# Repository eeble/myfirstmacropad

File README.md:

# myfirstmacropad
My First Macro Pad

I'll try to keep this updated.

<br />This work is licensed under a <a rel="license" href="http://creativecommons.org/licenses/by-sa/4.0/">Creative Commons Attribution-ShareAlike 4.0 International License</a>.

This macropad will use QMK as its firmware. QMK is also open source and available from https://qmk.fm/

### Front and Back renders

### BOM
Interactive [BOM](kicad/bom/ibom.html)

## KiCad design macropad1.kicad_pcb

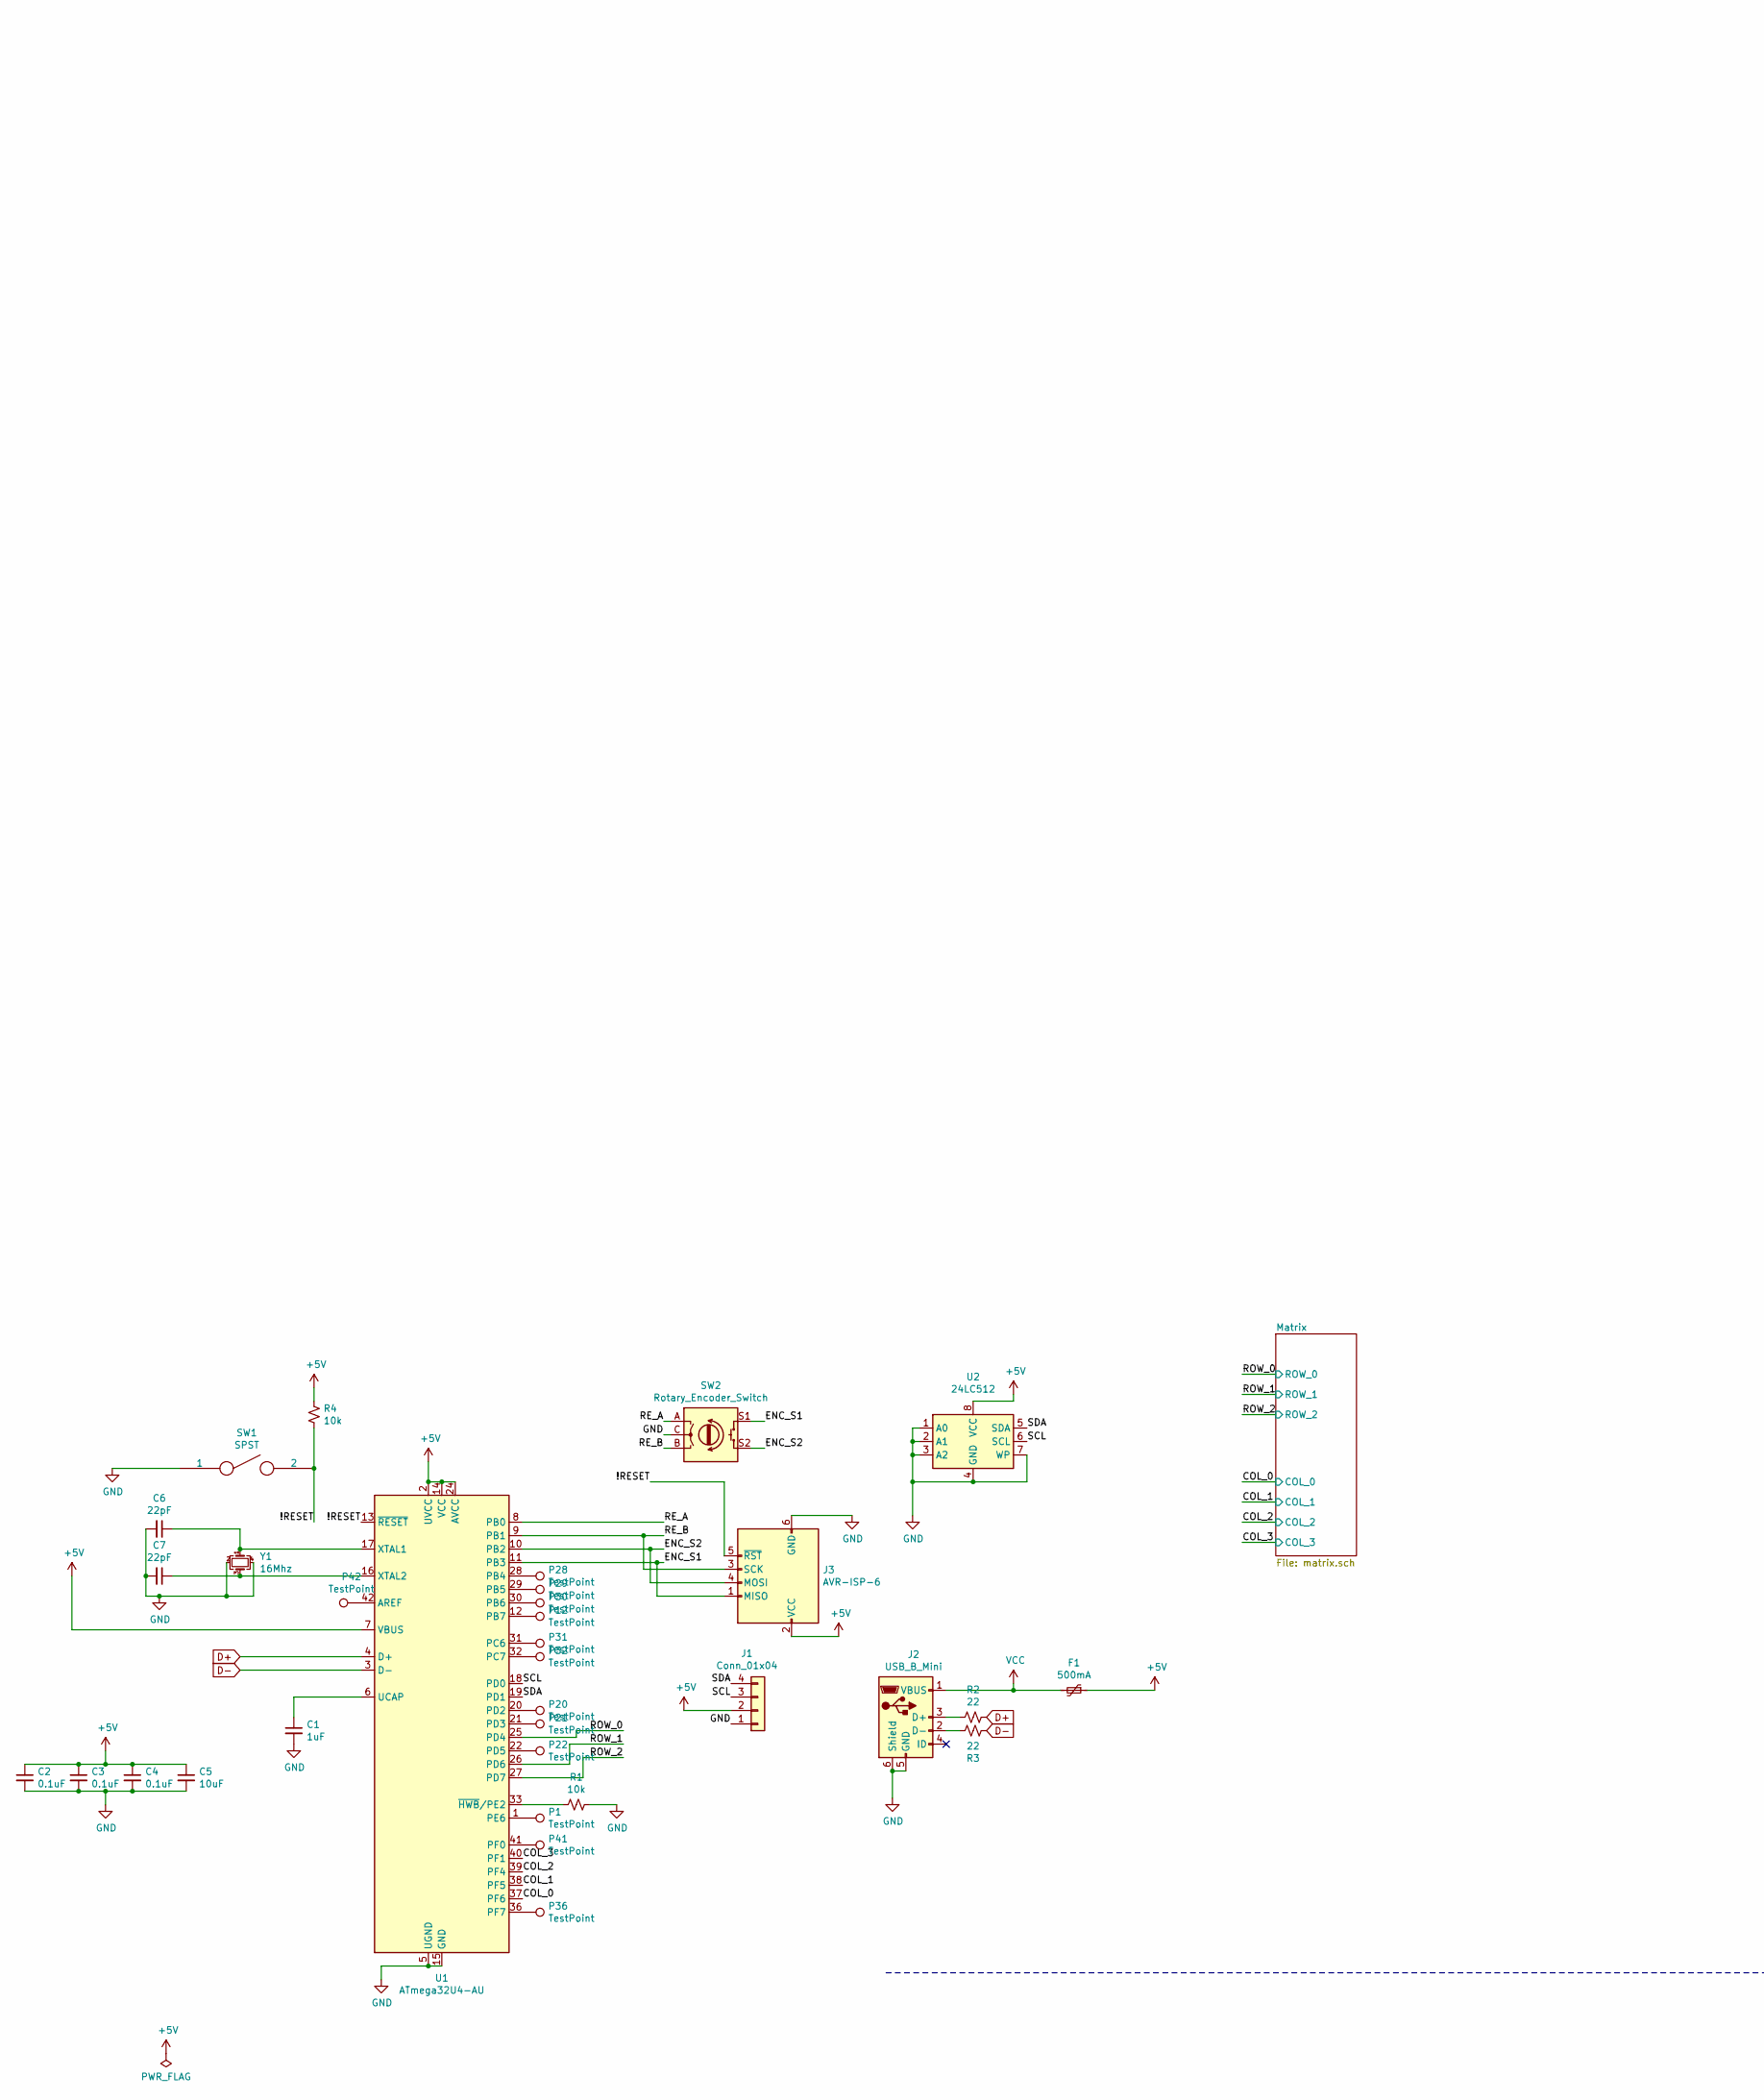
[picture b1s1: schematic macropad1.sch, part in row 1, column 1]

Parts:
C1: 1uF; C_0805_2012Metric
C2, C3, C4: 0.1uF; C_0805_2012Metric
C5: 10uF; C_0805_2012Metric
C6, C7: 22pF; C_0805_2012Metric
F1: 500mA; Fuse_1206_3216Metric
J1: Conn_01x04; OLED_0.91in_4pin
J2: USB_B_Mini; USB_Mini-B_Lumberg_2486_01_Horizontal
J3: AVR-ISP-6; PinHeader_2x03_P2.54mm_Vertical
P1, P12, P20, P21, P22, P28, P29, P30, P31, P32, P36, P41, P42: TestPoint; TestPoint_Pad_D1.0mm
R1, R4: 10k; R_0805_2012Metric
R2, R3: 22; R_0805_2012Metric
SW1: SPST; SW_SPST_REED_CT05-XXXX-G1
SW2: Rotary_Encoder_Switch; RotaryEncoder_Alps_EC11E-Switch_Vertical_H20mm
U1: ATmega32U4-AU; TQFP-44_10x10mm_P0.8mm
U2: 24LC512; TSSOP-8_4.4x3mm_P0.65mm
Y1: 16Mhz; Crystal_SMD_3225-4Pin_3.2x2.5mm_HandSoldering

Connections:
+5V: C2.1, C3.1, C4.1, C5.1, F1.1, J1.2, J3.2 (VCC), R4.1, U1.2 (UVCC), U1.7 (VBUS), U1.14 (VCC), U1.24 (AVCC), U1.34 (VCC), U1.44 (AVCC), U2.8 (VCC); also elsewhere on the board
/!RESET: J3.5 (~RST), R4.2, SW1.2, U1.13 (~RESET)
/COL_0: U1.37 (PF6); also elsewhere on the board
/COL_1: U1.38 (PF5); also elsewhere on the board
/COL_2: U1.39 (PF4); also elsewhere on the board
/COL_3: U1.40 (PF1); also elsewhere on the board
/ENC_S1: J3.1 (MISO), SW2.S1, U1.11 (PB3)
/ENC_S2: J3.4 (MOSI), SW2.S2, U1.10 (PB2)
/PWM1: P12.1, U1.12 (PB7); also elsewhere on the board
/RE_A: SW2.A, U1.8 (PB0)
/RE_B: J3.3 (SCK), SW2.B, U1.9 (PB1)
/ROW_0: U1.25 (PD4); also elsewhere on the board
/ROW_1: U1.26 (PD6); also elsewhere on the board
/ROW_2: U1.27 (PD7); also elsewhere on the board
/SCL: J1.3, U1.18 (PD0), U2.6 (SCL)
/SDA: J1.4, U1.19 (PD1), U2.5 (SDA)
/status_led: P22.1, U1.22 (PD5); also elsewhere on the board
D+: R2.1, U1.4 (D+)
D-: R3.2, U1.3 (D-)
GND: C1.2, C2.2, C3.2, C4.2, C5.2, C6.2, C7.2, J1.1, J2.5 (GND), J2.6 (Shield), J3.6 (GND), R1.1, SW1.1, SW2.C, U1.5 (UGND), U1.15 (GND), U1.23 (GND), U1.35 (GND), U1.43 (GND), U2.1 (A0), U2.2 (A1), U2.3 (A2), U2.4 (GND), U2.7 (WP), Y1.2, Y1.4; also elsewhere on the board
unnamed: C1.1, U1.6 (UCAP)
unnamed: C6.1, U1.17 (XTAL1), Y1.1
unnamed: C7.1, U1.16 (XTAL2), Y1.3
unnamed: J2.2 (D-), R3.1
unnamed: J2.3 (D+), R2.2
unnamed: P1.1, U1.1 (PE6)
unnamed: P20.1, U1.20 (PD2)
unnamed: P21.1, U1.21 (PD3)
unnamed: P28.1, U1.28 (PB4)
unnamed: P29.1, U1.29 (PB5)
unnamed: P30.1, U1.30 (PB6)
unnamed: P31.1, U1.31 (PC6)
unnamed: P32.1, U1.32 (PC7)
unnamed: P36.1, U1.36 (PF7)
unnamed: P41.1, U1.41 (PF0)
unnamed: P42.1, U1.42 (AREF)
unnamed: R1.2, U1.33 (~HWB~/PE2)
VCC: F1.2, J2.1 (VBUS)

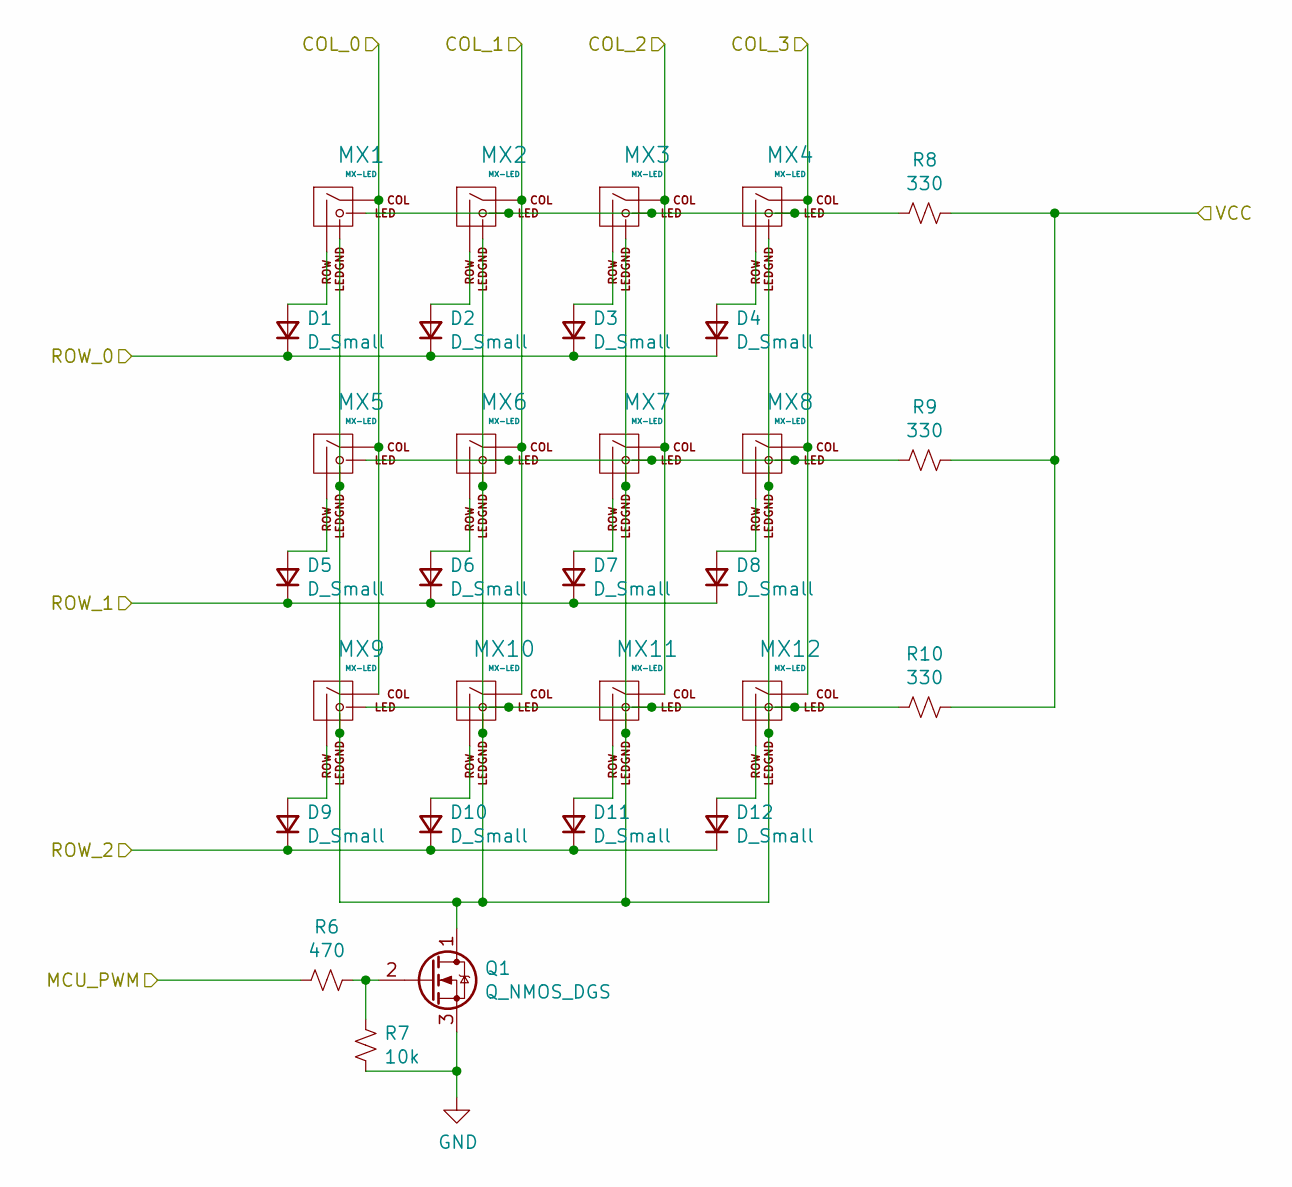
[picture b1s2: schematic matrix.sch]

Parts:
D1, D2, D3, D4, D5, D6, D7, D8, D9, D10, D11, D12: D_Small; D_SOD-123
MX1, MX2, MX3, MX4, MX5, MX6, MX7, MX8, MX9, MX10, MX11, MX12: MX-LED; MX-1U
Q1: Q_NMOS_DGS; SOT-723
R6: 470; R_0805_2012Metric
R7: 10k; R_0805_2012Metric
R8, R9, R10: 330; R_0805_2012Metric

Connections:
+5V: R8.1, R9.1, R10.1; also elsewhere on the board
/COL_0: MX1.1 (COL), MX5.1 (COL), MX9.1 (COL); also elsewhere on the board
/COL_1: MX2.1 (COL), MX6.1 (COL), MX10.1 (COL); also elsewhere on the board
/COL_2: MX3.1 (COL), MX7.1 (COL), MX11.1 (COL); also elsewhere on the board
/COL_3: MX4.1 (COL), MX8.1 (COL), MX12.1 (COL); also elsewhere on the board
/PWM1: R6.2; also elsewhere on the board
/ROW_0: D1.1 (K), D2.1 (K), D3.1 (K), D4.1 (K); also elsewhere on the board
/ROW_1: D5.1 (K), D6.1 (K), D7.1 (K), D8.1 (K); also elsewhere on the board
/ROW_2: D9.1 (K), D10.1 (K), D11.1 (K), D12.1 (K); also elsewhere on the board
GND: Q1.3 (S), R7.2; also elsewhere on the board
unnamed: D1.2 (A), MX1.2 (ROW)
unnamed: D2.2 (A), MX2.2 (ROW)
unnamed: D3.2 (A), MX3.2 (ROW)
unnamed: D4.2 (A), MX4.2 (ROW)
unnamed: D5.2 (A), MX5.2 (ROW)
unnamed: D6.2 (A), MX6.2 (ROW)
unnamed: D7.2 (A), MX7.2 (ROW)
unnamed: D8.2 (A), MX8.2 (ROW)
unnamed: D9.2 (A), MX9.2 (ROW)
unnamed: D10.2 (A), MX10.2 (ROW)
unnamed: D11.2 (A), MX11.2 (ROW)
unnamed: D12.2 (A), MX12.2 (ROW)
unnamed: MX1.3 (LED), MX2.3 (LED), MX3.3 (LED), MX4.3 (LED), R8.2
unnamed: MX1.4 (LEDGND), MX2.4 (LEDGND), MX3.4 (LEDGND), MX4.4 (LEDGND), MX5.4 (LEDGND), MX6.4 (LEDGND), MX7.4 (LEDGND), MX8.4 (LEDGND), MX9.4 (LEDGND), MX10.4 (LEDGND), MX11.4 (LEDGND), MX12.4 (LEDGND), Q1.1 (D)
unnamed: MX5.3 (LED), MX6.3 (LED), MX7.3 (LED), MX8.3 (LED), R9.2
unnamed: MX9.3 (LED), MX10.3 (LED), MX11.3 (LED), MX12.3 (LED), R10.2
unnamed: Q1.2 (G), R6.1, R7.1

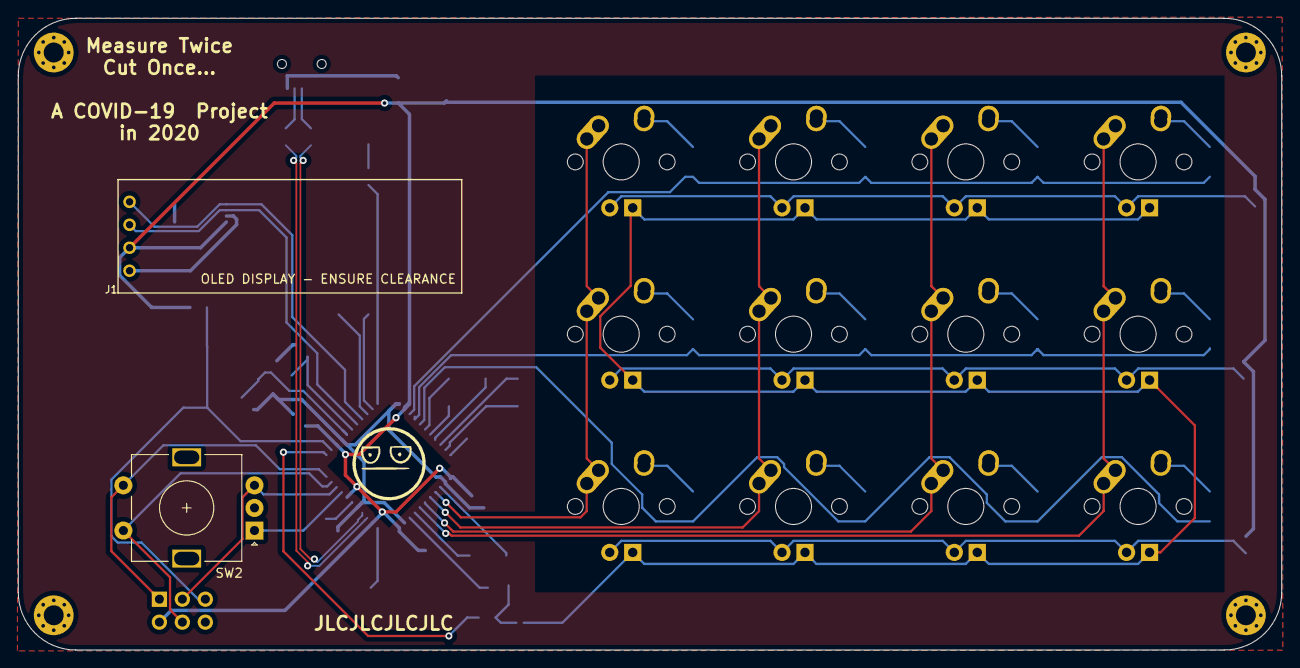
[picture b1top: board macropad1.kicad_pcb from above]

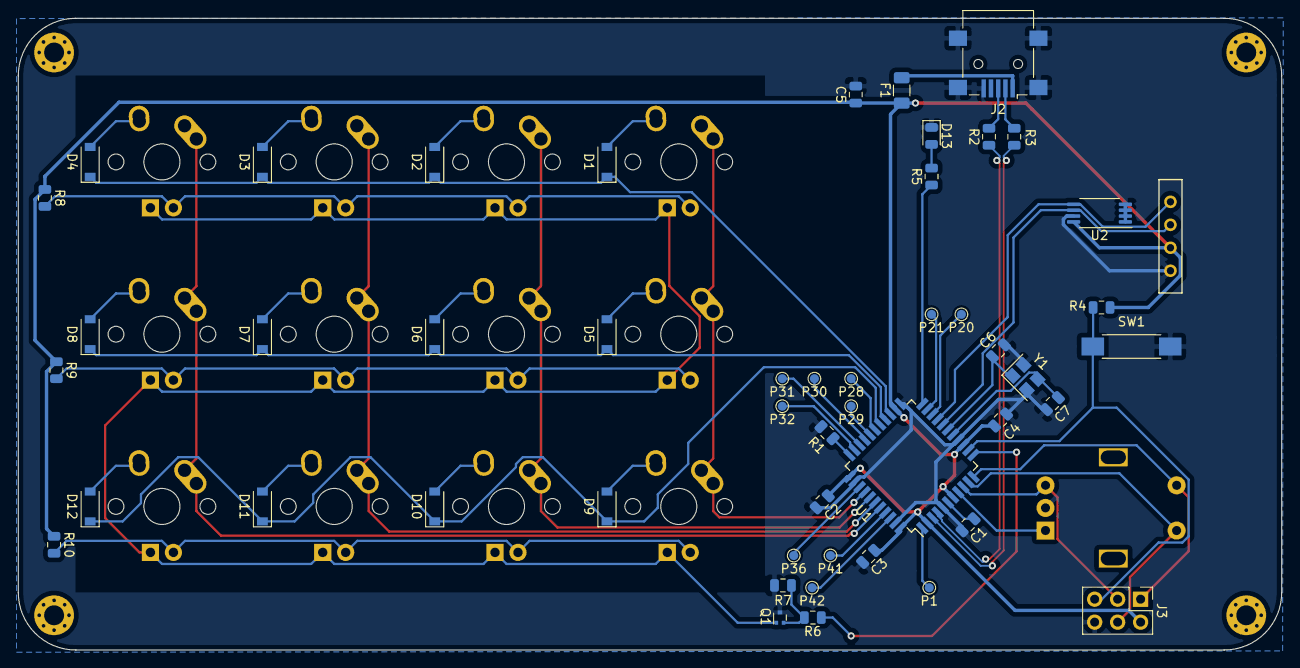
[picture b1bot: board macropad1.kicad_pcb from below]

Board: 2 copper layers, 139.7 x 69.8 mm, 63 parts (49 on the bottom side), 56 nets.

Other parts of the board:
D13: LED; LED_0805_2012Metric
R5: 330; R_0805_2012Metric

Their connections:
/status_led: R5.1; also elsewhere on the board
GND: D13.1; also elsewhere on the board
unnamed: D13.2, R5.2

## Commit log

2020-08-29 Initial import
2020-08-31 Ready for prototyping
2020-09-02 Added artwork lib and eeprom
2020-09-02 Added board pics
2020-09-13 Fixes D+/D- swap and adds ISP header
    Also moves some components around for better layout
2020-09-13 Adds testpads for all unused pins on MCU
2020-09-13 Repours copper fill and updates images
2020-09-13 Reworks location of traces for ISP header
2020-09-13 Re-ran DRC
2020-09-13 Adds single color backlighting to each key :)
2020-09-13 Produced files for JCLPCB
2020-09-15 Adds switches to the 3d model
2020-09-23 Adds kicad directory for kicad stuff
2020-09-23 Put README.md back where it belongs
2020-09-23 Move pictures as well
2020-09-23 Adds qmk keyboard code
2020-09-25 fixes matrix and adds oled poc
2020-12-09 Adds iBom and final revision of board
    Puts holes in the right place for the case
    Adds proper backlight support with a properly sized mosfet (tiny)
    Double checks dimensions
2020-12-09 Adds link to BOM in README.md
2020-12-09 re-saved file
